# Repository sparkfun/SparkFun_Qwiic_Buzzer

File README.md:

SparkFun Qwiic Buzzer
========================================

[*SparkFun Qwiic Buzzer (BOB-24474)*](https://www.sparkfun.com/products/24474)

The SparkFun Qwiic Buzzer adds simple beeps and buzzes to your projects via I<sup>2</sup>C Make some noises to alert you when something interesting (or urgent) happens. Simply connect a Qwiic cable and load up some pre-written code to an Arduino to start making noises!

The board includes an ATtiny84 with custom firmware to control the piezoelectric buzzer over I<sup>2</sup>C. Utilizing our handy Qwiic system, no soldering is required to connect it to the rest of your system. However, we still broke out 0.1"-spaced PTH pads if you prefer to use a breadboard to access the board's I2C, power, trigger, and reset pins on the board's edge. A 2.2k&ohm; pull-up resistor is included on the data and clock lines. 

A set of transistors control the buzzer's volume. At full volume, it allows the full current of about ~95mA, which makes it _really_ loud. A flyback diode is included to discharge any energy remaining when the buzzer is turned off. For those who want to control the loudness of the buzzer, a footprint is available to solder a custom PTH resistor to one of the transistors. Just make sure to cut the jumper labeled "JP1." Two LEDs are also included on the board for power and status. 

We've written an Arduino Library to control the volume, frequency, duration, and I<sup>2</sup>C address. There are even examples of how to play a quick melody and sweet sound effects! You can download the library through the Arduino library manager by searching 'SparkFun Qwiic Buzzer,' or you can get the GitHub repo as a .zip to install the library from there manually. For those who want a simple buzz without an Arduino, you can also make noise by simply grounding the trigger pin! We've even ported the library as a Python package! 

This board is great for adding a simple audible sound to your projects. Pair the board with the Qwiic RTC to make an alarm clock, play a tune with the Qwiic RFID, or add a sound effect to your robot. So what are you waiting for?!? Start making some noise in your projects with the SparkFun Qwiic Buzzer!

Repository Contents
-------------------

* **.github/workflows** - YAML files used for GitHub Actions and GitHub Pages/mkdocs
* **/Firmware** - ATtiny84 Firmware
* **/Hardware** - Eagle design files (.brd, .sch)
  * **/Production** - Production panel files (.brd)
* **/docs** - Online documentation files
  * **/assets** - Folder containing all the file assets used for product documentation
    * **/board_files** - Copy of design files used for product documentation
    * **/component_documentation** - Datasheets and manuals for hardware components
    * **/img** - Images for product documentation
  * **/github** - Files stating how to contribute and filing issues used for product documentation
  * **/javascript** - Folder containing custom javascript used for product documentation
  * **/stylesheet** - Folder containing CSS files used for product documentation
* **/overrides** - Customization files used for product documentation
  * **/.icons** - Icons used for GitHub used for product documentation
  * **./partials** - Used for product documentation

Documentation
--------------

* **[Installing an Arduino Library Guide](https://learn.sparkfun.com/tutorials/installing-an-arduino-library)** - Basic information on how to install an Arduino library.
* **[Library](https://github.com/sparkfun/SparkFun_Qwiic_Buzzer_Arduino_Library)** - Arduino library for the Qwiic Buzzer.
* **[Hookup Guide](https://docs.sparkfun.com/SparkFun_Qwiic_Buzzer)** - Basic hookup guide for the  Qwiic Buzzer.

Product Versions
----------------
* [BOB-24474](https://www.sparkfun.com/products/24474) - v1.0

Version History
---------------
* v1.0 - Initial release

License Information
-------------------

This product is _**open source**_! 

Please review the LICENSE.md file for license information. 

If you have any questions or concerns on licensing, please contact technical support on our [SparkFun forums](https://forum.sparkfun.com/viewforum.php?f=152).

Distributed as-is; no warranty is given.

- Your friends at SparkFun.

_<COLLABORATION CREDIT>_

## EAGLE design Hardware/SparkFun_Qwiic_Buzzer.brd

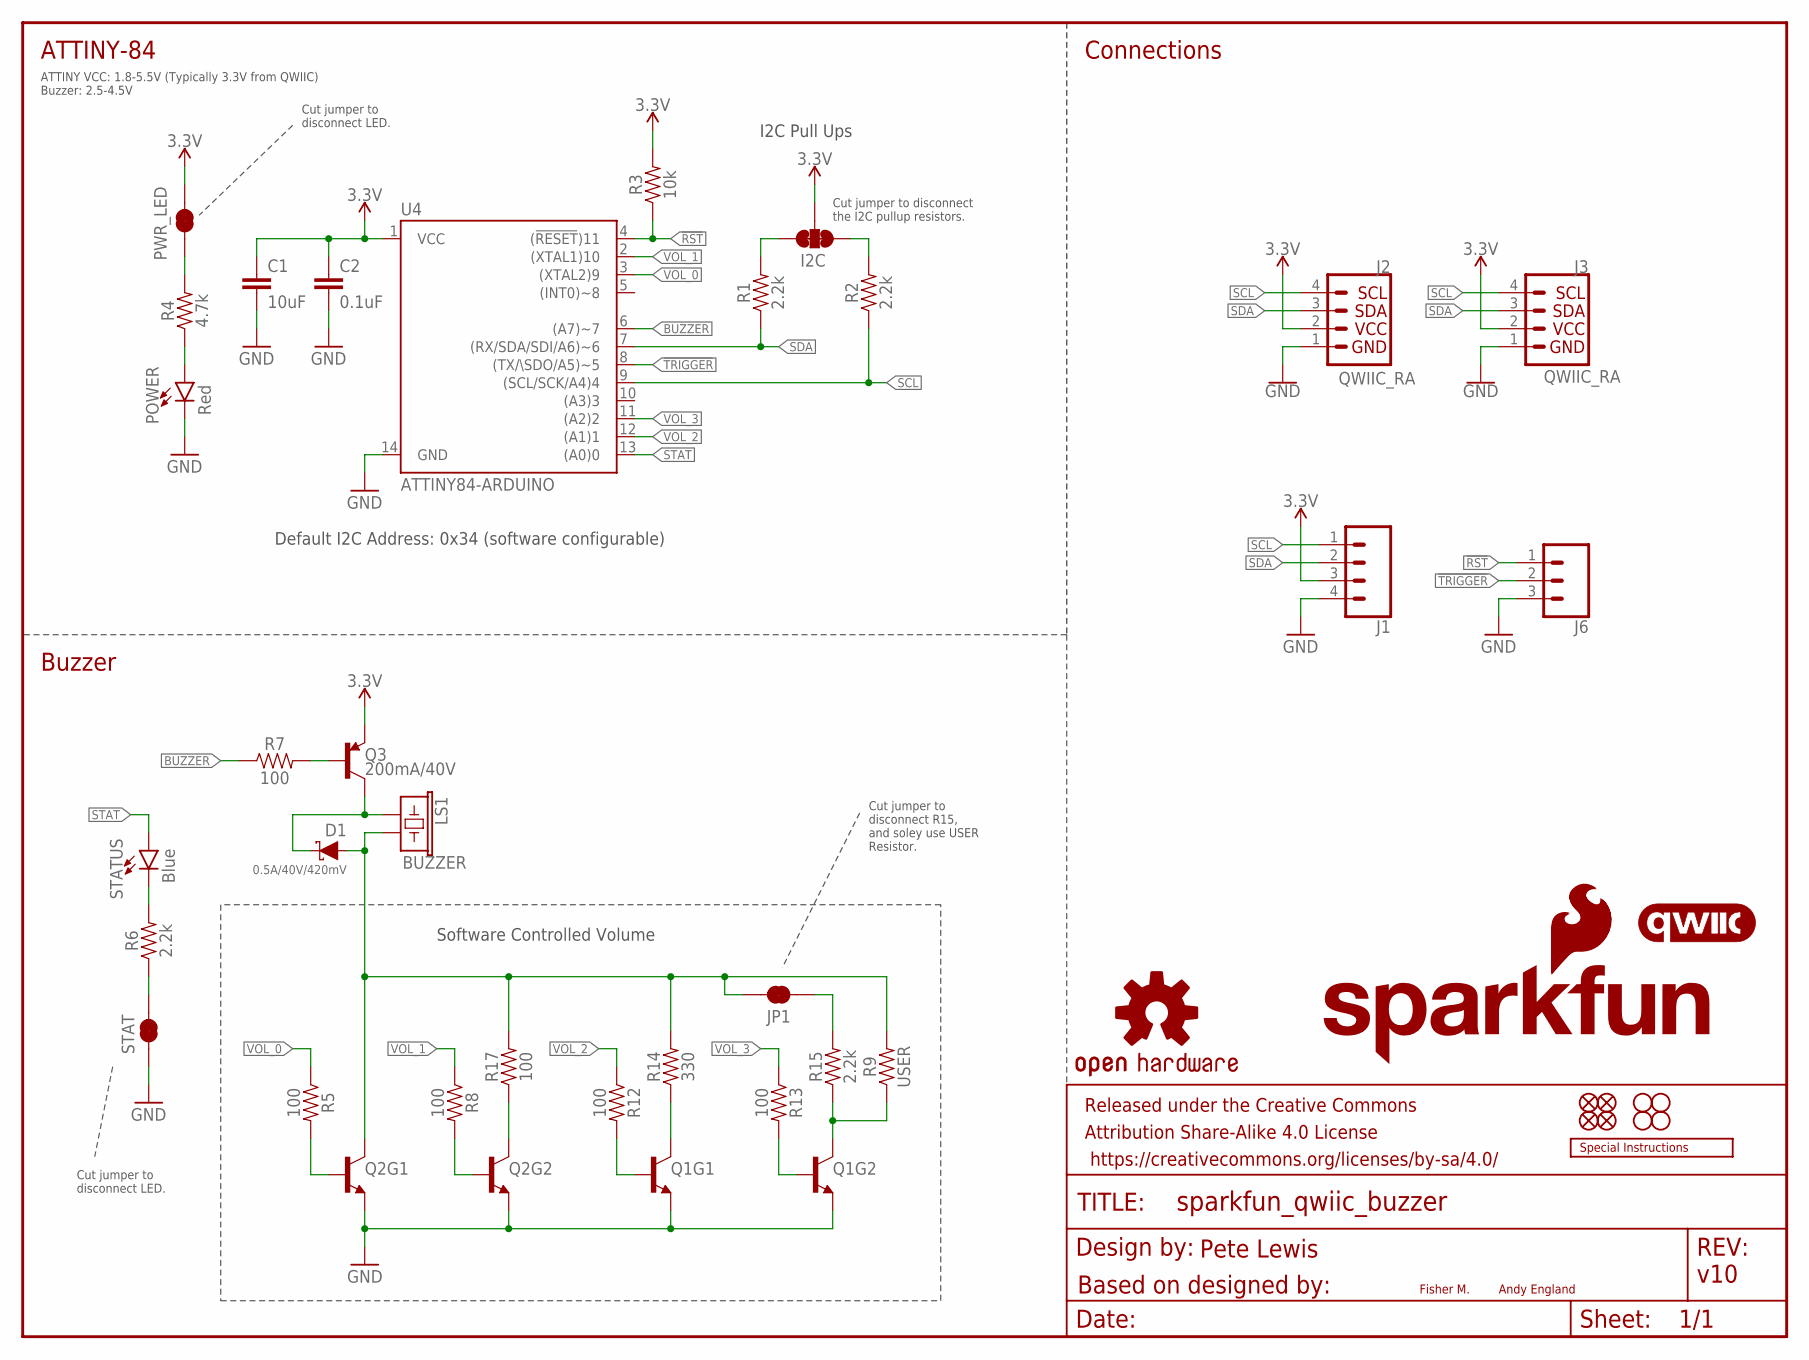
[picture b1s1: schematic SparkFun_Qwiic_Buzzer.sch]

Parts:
C1: 10uF; 0402-TIGHT
C2: 0.1uF; 0402-TIGHT
D1: 0.5A/40V/420mV; SOD-323
FRAME1: FRAME-LETTER; CREATIVE_COMMONS
H1, H2, H3, H4: STAND-OFF
I2C: JUMPER-SMT_3_2-NC_TRACE_SILK; SMT-JUMPER_3_2-NC_TRACE_SILK
J1: CONN_041X04_NO_SILK; 1X04_NO_SILK
J2, J3: QWIIC_RA; JST04_1MM_RA
J6: CONN_031X03_NO_SILK; 1X03_NO_SILK
JP1: JUMPER-SMT_2_NC_TRACE_SILK; SMT-JUMPER_2_NC_TRACE_SILK
JP2, JP6, JP8, JP9: FIDUCIALUFIDUCIAL; FIDUCIAL-MICRO
LOGO1: OSHW-LOGOMINI; OSHW-LOGO-MINI
LOGO2: SFE_LOGO_NAME_FLAME.1_INCH; SFE_LOGO_NAME_FLAME_.1
LOGO3: SPECIAL_INSTRUCTIONS-ORDERING; ORDERING_INSTRUCTIONS
LOGO4: SFE_LOGO_FLAME.1_INCH; SFE_LOGO_FLAME_.1
LOGO5: QWIIC_LOGO_4MM; QWIIC_4MM
LS1: BUZZER; BUZZER-CCV
POWER: Red; LED-0603
PWR_LED: PWR_LED; SMT-JUMPER_2_NC_TRACE_SILK
Q1, Q2: TRANS_NPN_DUAL-MBT3904DW1T1; SC70-6
Q3: 200mA/40V; SOT23-3
R1, R2, R6, R15: 2.2k; 0402-TIGHT
R3: 10k; 0402-TIGHT
R4: 4.7k; 0402-TIGHT
R5, R7, R8, R12, R13, R17: 100; 0402-TIGHT
R9: USER; AXIAL-0.3
R14: 330; 0402-TIGHT
STAT: PWR_LED; SMT-JUMPER_2_NC_TRACE_SILK
STATUS: Blue; LED-0603
U4: ATTINY84-ARDUINO; SO14

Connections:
3.3V: C1.1, C2.1, I2C.2, J1.3, J2.2, J3.2, PWR_LED.2, Q3.2 (E), R3.2, U4.1 (VCC)
!RST: J6.1, R3.1, U4.4 ((!RESET!)11)
!TRIGGER!: J6.2, U4.8 ((TX/\SDO/A5)~5)
BUZZER: R7.1, U4.6 ((A7)~7)
GND: C1.2, C2.2, J1.4, J2.1, J3.1, J6.3, POWER.C, Q1.1 (E), Q1.4 (E), Q2.1 (E), Q2.4 (E), STAT.1, U4.14 (GND)
unnamed: PWR_LED.1, R4.2
unnamed: Q2.5 (B), R5.2
unnamed: POWER.A, R4.1
unnamed: D1.A, JP1.2, LS1.- (2), Q2.3 (C), R9.P$2 (2), R14.2, R17.2
unnamed: Q3.1 (B), R7.2
unnamed: D1.C, LS1.+ (1), Q3.3 (C)
unnamed: R6.2, STATUS.C
unnamed: R6.1, STAT.2
unnamed: Q1.2 (B), R13.2
unnamed: Q1.5 (B), R12.2
unnamed: Q2.2 (B), R8.2
unnamed: Q2.6 (C), R17.1
unnamed: Q1.3 (C), R14.1
unnamed: Q1.6 (C), R9.P$1 (1), R15.1
unnamed: JP1.1, R15.2
SCL: J1.1, J2.4, J3.4, R2.1, U4.9 ((SCL/SCK/A4)4)
SCL_PU1: I2C.1, R2.2
SDA: J1.2, J2.3, J3.3, R1.1, U4.7 ((RX/SDA/SDI/A6)~6)
SDA_PU1: I2C.3, R1.2
STAT: STATUS.A, U4.13 ((A0)0)
VOL_0: R5.1, U4.3 ((XTAL2)9)
VOL_1: R8.1, U4.2 ((XTAL1)10)
VOL_2: R12.1, U4.12 ((A1)1)
VOL_3: R13.1, U4.11 ((A2)2)

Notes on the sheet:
v10
Connections
Cut jumper to disconnect the I2C pullup resistors.
I2C Pull Ups
Fisher M.
Andy England
ATTINY-84
Buzzer
ATTINY VCC: 1.8-5.5V (Typically 3.3V from QWIIC) Buzzer: 2.5-4.5V
Based on designed by:
Pete Lewis
Software Controlled Volume
Cut jumper to disconnect LED.
Default I2C Address: 0x34 (software configurable)
Cut jumper to disconnect R15, and soley use USER Resistor.

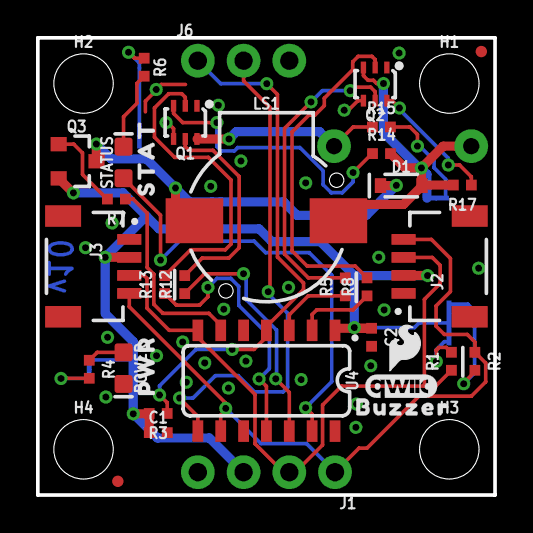
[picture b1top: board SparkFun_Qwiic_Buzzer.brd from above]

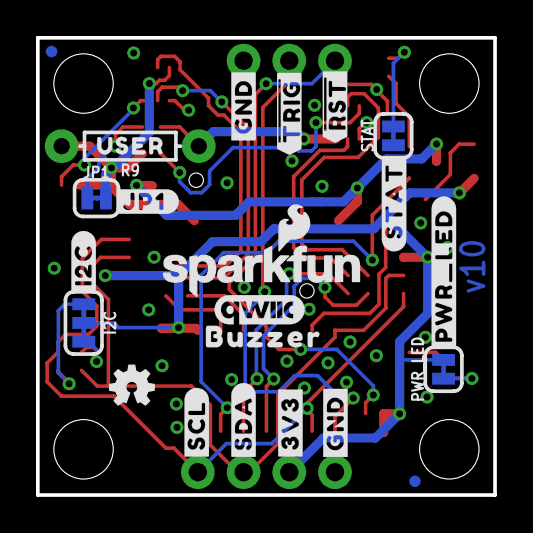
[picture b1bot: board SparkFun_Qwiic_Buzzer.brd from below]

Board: 2 copper layers, 25.4 x 25.4 mm, 63 parts (23 on the bottom side), 29 nets.

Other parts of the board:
U$1: STAT0
U$2, U$10: #GND#0
U$5: #PWR_LED#13
U$6: #JP1#14
U$7: #STAT#3
U$8: USER12
U$9: PWR0
U$11: #I2C#0
U$12: ##RST##7
U$13: BUZZER1
U$15: ##TRIG##6
U$16: QWIIC_5MM
U$17: #3V3#0
U$18: #SCL#0
U$19: #SDA#0
U$22: BUZZER14

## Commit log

2023-12-07 Layout started
2023-12-08 Layout done
2023-12-08 updated miso to poci
    both net names and board header silk
2023-12-08 Aligned header to be breadboard friendly
2023-12-08 add ordering instructions
2023-12-08 text only label for USER resistor
2023-12-08 INT pin anular ring correction
2023-12-08 Measures
2023-12-08 replace parts from old libraries
    -fids and gnd symbols
2023-12-08 default i2c address is 0x34
    added note to sch.
2023-12-08 approve drc error
2023-12-08 more ordering instructions
2023-12-11 add buzzer datasheet
2023-12-11 group review pre-meeting
    -add flyback diode
    -add tPlace lines to divide tightly packed passives
    -add 10uF cap on 3V3 rail
    -corrected name on I2C Jumper
    -Added JP1 to allow user to easily remove R15 resistor when using USER PTH resistor for volume control
    -fixes some acid traps on poci and rst headers
2023-12-11 reduced size of qwiic logo and buzzer test on bottom silk
2023-12-12 Corrected GND header silk label
    -rotated GND header silk label to match others
    -updated VCC note in sch to show typically 3.3V via QWIIC.
2023-12-12 Added note about SPI - only for programming
    -This product will not accept commands via SPI. These connections are only broken out for firmware programming.
2023-12-12 post review tweaks
    -removed INT pin feature (both header pin and pullup resistor)
    -changed TRIGGER pin to use POCI pin. It will be there for programming as needed, but this naming omits any mention of SPI, making it really clear this doesn't do SPI.
2023-12-12 finalized resistor values on vol control
2023-12-13 STAT LED moved to GPIO
    -This way it won't be dimmed by the buzzers frequency and can more precisely be controlled via firmware.
2023-12-13 routing nudges
2023-12-14 Production Panel v10
2023-12-14 Bringing in copy of Button Firmware
2023-12-14 small tweaks to get hacked button working as buzzer
2023-12-14 final review tweaks - no copper changes
    -re-order position of 0.1uF and 10uF Caps
    -re-order vol resistors
    -redo measures so they are better
    -added QWIIC logo to sch
2023-12-14 re-panelized and re-cammed
    -all gerbers showed no diffs, so we're good to go.
2023-12-22 change folder name
2023-12-22 header file name change
2023-12-22 replacing pulseCycleTime with toneFrequency
2023-12-22 registermap re-order (toneFrequency)
    -toneFrequency is now the 3rd item in the register memory map
2023-12-22 name change ledconfig to buzzerconfig
2023-12-22 removing unnecessary tone()
    -not needed or used in readSystemSettings, so let's get this out of here!
2023-12-22 namechange ledBrightness to BuzzerVolume
2023-12-22 namechange brightness to volume
2023-12-22 namechange ledpin to buzzerPin
2023-12-22 register map re-order (volume)
2023-12-22 namechange onboardLED to onboardBUZZER
2023-12-22 Added noTone() to turn off tone when not in use
2023-12-22 remove a lot of button specific stuff
    like interrupt stuff, que stuff, and LED pulsing/fading stuff
2023-12-22 new default address 0x34
2024-01-10 frequency working as MSB and LSB
2024-01-11 frequency and duration working
2024-01-11 removing some more button stuff and changing wording
2024-01-11 volume working
2024-01-11 Status LED working
2024-01-11 trigger pin working
2024-01-12 ex6 save settings working
2024-01-12 ex7 play melody working
    -also added some stuff to catch "rest notes" (that is, when the user sends in a frequency of 0. These extra checks allow for quiet rests without any clicking on the buzzer (caused by tone or volume c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
2024-01-12 v0.0.1 firmware - compiled hex
2024-01-15 updated constant naming styles
2024-01-17 header guards added
2024-01-17 updates, round 1
    -added header gaurds
    -#includes moved into buzzer.h
    -included <Arduino.h> in buzzer.h
    -constants naming updated
    -moved interrupt functions into main INO file
    -deleted interrupts.h file
2024-01-17 comment alignment and cleanup
2024-01-17 on a fresh EEPROM, default to volume 4
    -so trigger pin works out of the box, even without running save settings example
2024-01-17 moved from struct to class
    updates names, formatting, comments
2024-01-18 Duration bug
    -duration wasn't getting saved properly to EEPROM or updated from map. This led to settings not being effective when using TRIGGER pin.
    -Changed checkDuration to return true/false, and moved the call to reset outside of that funtion.
    -Changed a bit how trigger pin is handled in main loop. It now reacts properly to momentary vs one-shot mode.
2024-01-18 BOM change - control resistors changed to 100 ohm
    R7, R5, R17, R12, R9
2024-01-18 Allows multiple calls to on to take effect
2024-01-22 incrementing device ID
    -to differentiate it from other qwiic products with device IDs (the button is the only one I could find and its was 0x5D)
2024-01-23 changed "diffferent" logic to update on the spot
2024-01-23 simplified checkDuration
2024-01-23 Class instance variables now prefixed with "_"
    And since I need to look at _buzzerActiveFlag in the main loop, I created a function to get it out of the library. ("active()" is new and returns _buzzerActiveFlag).
2024-01-23 adding define for resonant frequency
    -also, class variables all get updated by readSystemSettings() and/or recordSystemSettings(), so their initial values are not being used. Removing instantiated values to avoid confusion.
2024-01-23 registerMap values to start as 0x00 to avoid confusion
    -this all get updated on readSystemSettings() and/or recordSystemSettings(), so better to start them at 0x00
2024-01-23 statusLedPin and buzzerPin moved into class variables
    Also updated setupPins to accept these two pins.
2024-01-23 Tested SLEEP_MODE_PWR_DOWN and it stops responding to I2C
2024-01-23 correcting protectionMap
    also mapDuration should default to 0 since I'm doing bitwise OR below
2024-01-23 default case catch on volume switch
2024-01-23 status LED can just stat OUTPUT all the time
2024-01-23 removing duration when using tone(), fixed checkDuration
    -because this is handled with duration and reset, we don't need to send it to tone()
    -uncovered and fixed a problem with checkDuration - it was returning the opposite of what it should be. fixed now.
2024-01-23 added a call to noTone() when frequency is set to 0
2024-01-23 Trigger pin now a non-blocker and reacts to transitions
    -Trigger pin now reacts to debounce transitions, and so do not block any incoming I2C register writes
2024-01-23 update old comments about trigger
2024-01-23 updateFlag should only be set if numberOfBytesReceived > 1
    when we receive an I2C event message, updateFlag should only be set if numberOfBytesReceived > 1
2024-01-23 better naming
    "x" is now "registerOffset"
2024-01-24 factory reset added
    -hold down trigger pin on boot up (for 1000ms), and this will reset settings EEPROM values to 0xFF.
2024-01-24 formatter and made class variables private
2024-01-24 moved and organized code into header and cpp files
2024-01-25 Updated compiled HEX (temp for production test dev)
2024-01-25 minor final-ish updates
    -reduced some code two single lines when dealing with MSB and LSB of a setting
    -removed unnecessary {} from single line statements
    -status LED now only comes on when there both non-zer values for volume and frequency.
    -updated some types (uint32_t and bool)
2024-01-26 updated compiled hex for production
2024-02-14 Push initial tutorial for GitHub Pages
2024-02-15 Clean up
2024-03-15 Deployed a920521 with MkDocs version: 1.5.3
2024-10-28 Add cookies
2024-10-29 Deployed 2d58684 with MkDocs version: 1.6.1

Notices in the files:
parts and their libraries:
SparkFun-Capacitors: Licensing: Creative Commons ShareAlike 4.0 International - https://creativecommons.org/licenses/by-sa/4.0
SparkFun-Aesthetics: Released under the Creative Commons Attribution Share-Alike 4.0 License
SparkFun-Aesthetics: https://creativecommons.org/licenses/by-sa/4.0
